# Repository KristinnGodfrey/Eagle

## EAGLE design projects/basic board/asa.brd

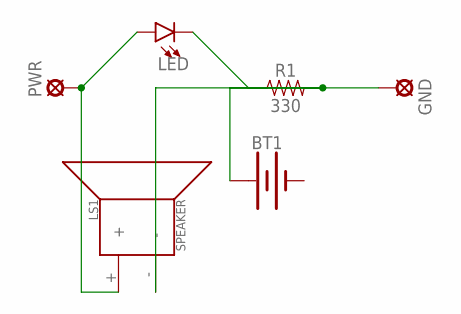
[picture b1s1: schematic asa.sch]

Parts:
BT1: BATTERY-12MM_PTH; BATTCON_12MM_PTH
GND: LSP11
LED: LED3MM; LED_3MM
LS1: SPEAKER; PCB_MOUNT_SPEAKER
PWR: LSP11
R1: 330; AXIAL-0.3

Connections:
-: BT1.GND (-)
unnamed: LED.A, LS1.+, PWR.MP
unnamed: LED.K (C), R1.P$1 (1)
unnamed: BT1.VCC@1 (+), GND.MP, LS1.-, R1.P$2 (2)

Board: 2 copper layers, 6 parts (0 on the bottom side), 3 nets, no tracks yet.

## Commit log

2020-10-05 added projects
2020-10-05 added project files
2020-10-05 removed dependencies

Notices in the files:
parts and their libraries:
SparkFun-Batteries: Licensing: Creative Commons ShareAlike 4.0 International - https://creativecommons.org/licenses/by-sa/4.0
